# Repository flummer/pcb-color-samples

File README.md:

# PCB Color, Thickness and Material Samples

These are a collection of color, thickness and material samples designed in KiCad. For a all the details, please see the [post about these samples at hackmeister.dk](https://www.hackmeister.dk/2020/02/pcb-color-thickness-and-material-samples/).

## License

The contents of this repository is released under the following licence:

 * the "Creative Commons Attribution-ShareAlike 4.0 International License"
   (CC BY-SA 4.0) full text of this license is included in the LICENSE file
   and a copy can also be found at
   http://creativecommons.org/licenses/by-sa/4.0/

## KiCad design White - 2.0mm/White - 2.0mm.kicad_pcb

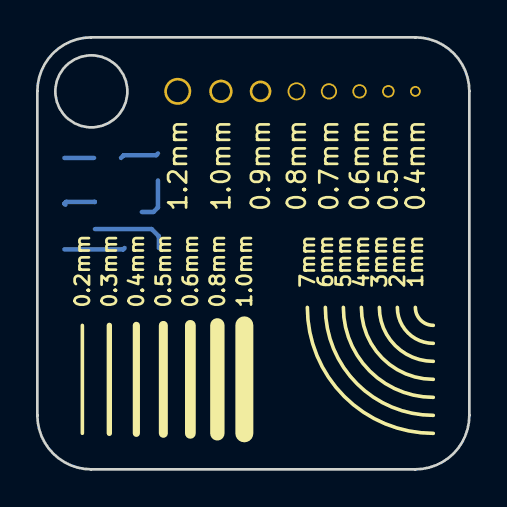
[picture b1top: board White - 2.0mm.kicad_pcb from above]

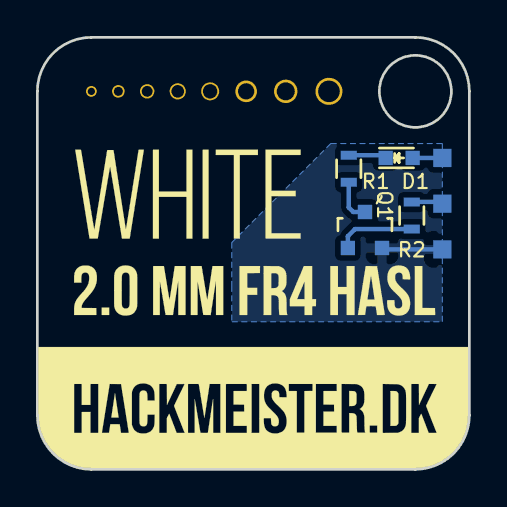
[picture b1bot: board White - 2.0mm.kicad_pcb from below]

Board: 2 copper layers, 24.0 x 24.0 mm, 7 parts (7 on the bottom side), 6 nets.

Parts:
D1: LED; LED_0603
P1, P2, P3: CONN_01X01; Small_SMD_Proto_Pad
Q1: BC817-40; SOT-23
R1, R2: R; R_0603

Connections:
GND: P3.1, Q1.2
unnamed: D1.1, R1.1
unnamed: P1.1, R2.2
unnamed: Q1.1, R2.1
unnamed: Q1.3, R1.2
VCC: D1.2, P2.1

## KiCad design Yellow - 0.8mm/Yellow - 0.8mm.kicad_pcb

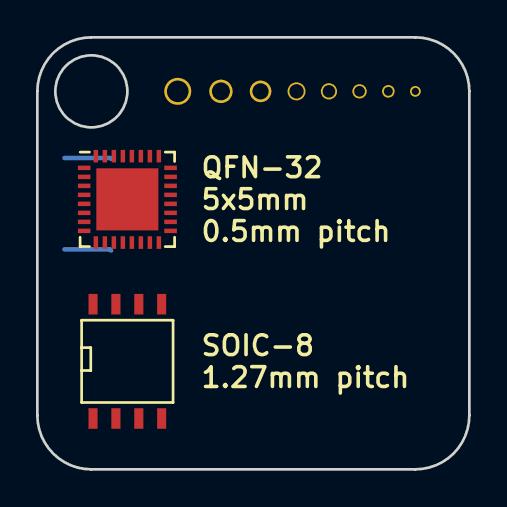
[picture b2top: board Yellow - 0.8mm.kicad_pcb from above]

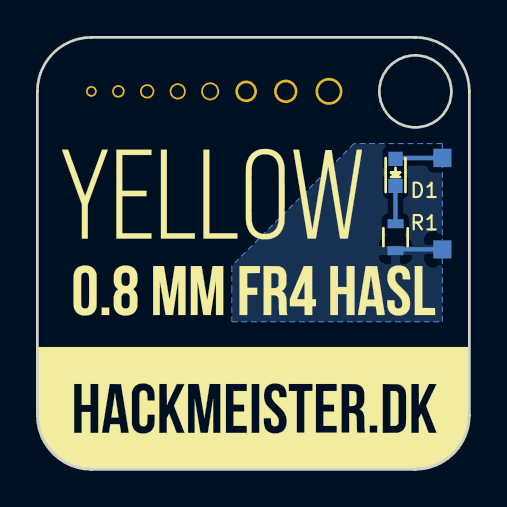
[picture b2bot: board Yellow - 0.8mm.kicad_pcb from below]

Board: 2 copper layers, 24.0 x 24.0 mm, 4 parts (4 on the bottom side), 3 nets.

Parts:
D1: LED; LED_0603
P1, P3: CONN_01X01; Small_SMD_Proto_Pad
R1: R; R_0603

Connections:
GND: P3.1, R1.2
unnamed: D1.1, R1.1
VCC: D1.2, P1.1

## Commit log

2020-02-22 Added readme and license
